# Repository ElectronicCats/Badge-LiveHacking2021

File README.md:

# Badge LiveHacking 2021

## Tecnologia

- Raspberry Pico
- LEDs
- Button
- USB

## Links

- [Raspberry Pico](https://www.raspberrypi.org/products/raspberry-pi-pico/)

## Agradecimientos
¿Quieres dar las gracias? Etiqueta a estas empresas en redes sociales y muestrales tu badge, gracias a ellos es posible

- [Mercado Libre](https://www.mercadolibre.com.mx/)
- [ElectronicCats](https://electroniccats.com/)

## License

Electronic Cats invests time and resources providing this open source design, please support Electronic Cats and open-source hardware by purchasing products from Electronic Cats!

Designed by Electronic Cats.

Hardware released under an CERN Open Hardware Licence v1.2. See the LICENSE_HARDWARE file for more information.

Electronic Cats is a registered trademark, please do not use if you sell these PCBs.

August 2021

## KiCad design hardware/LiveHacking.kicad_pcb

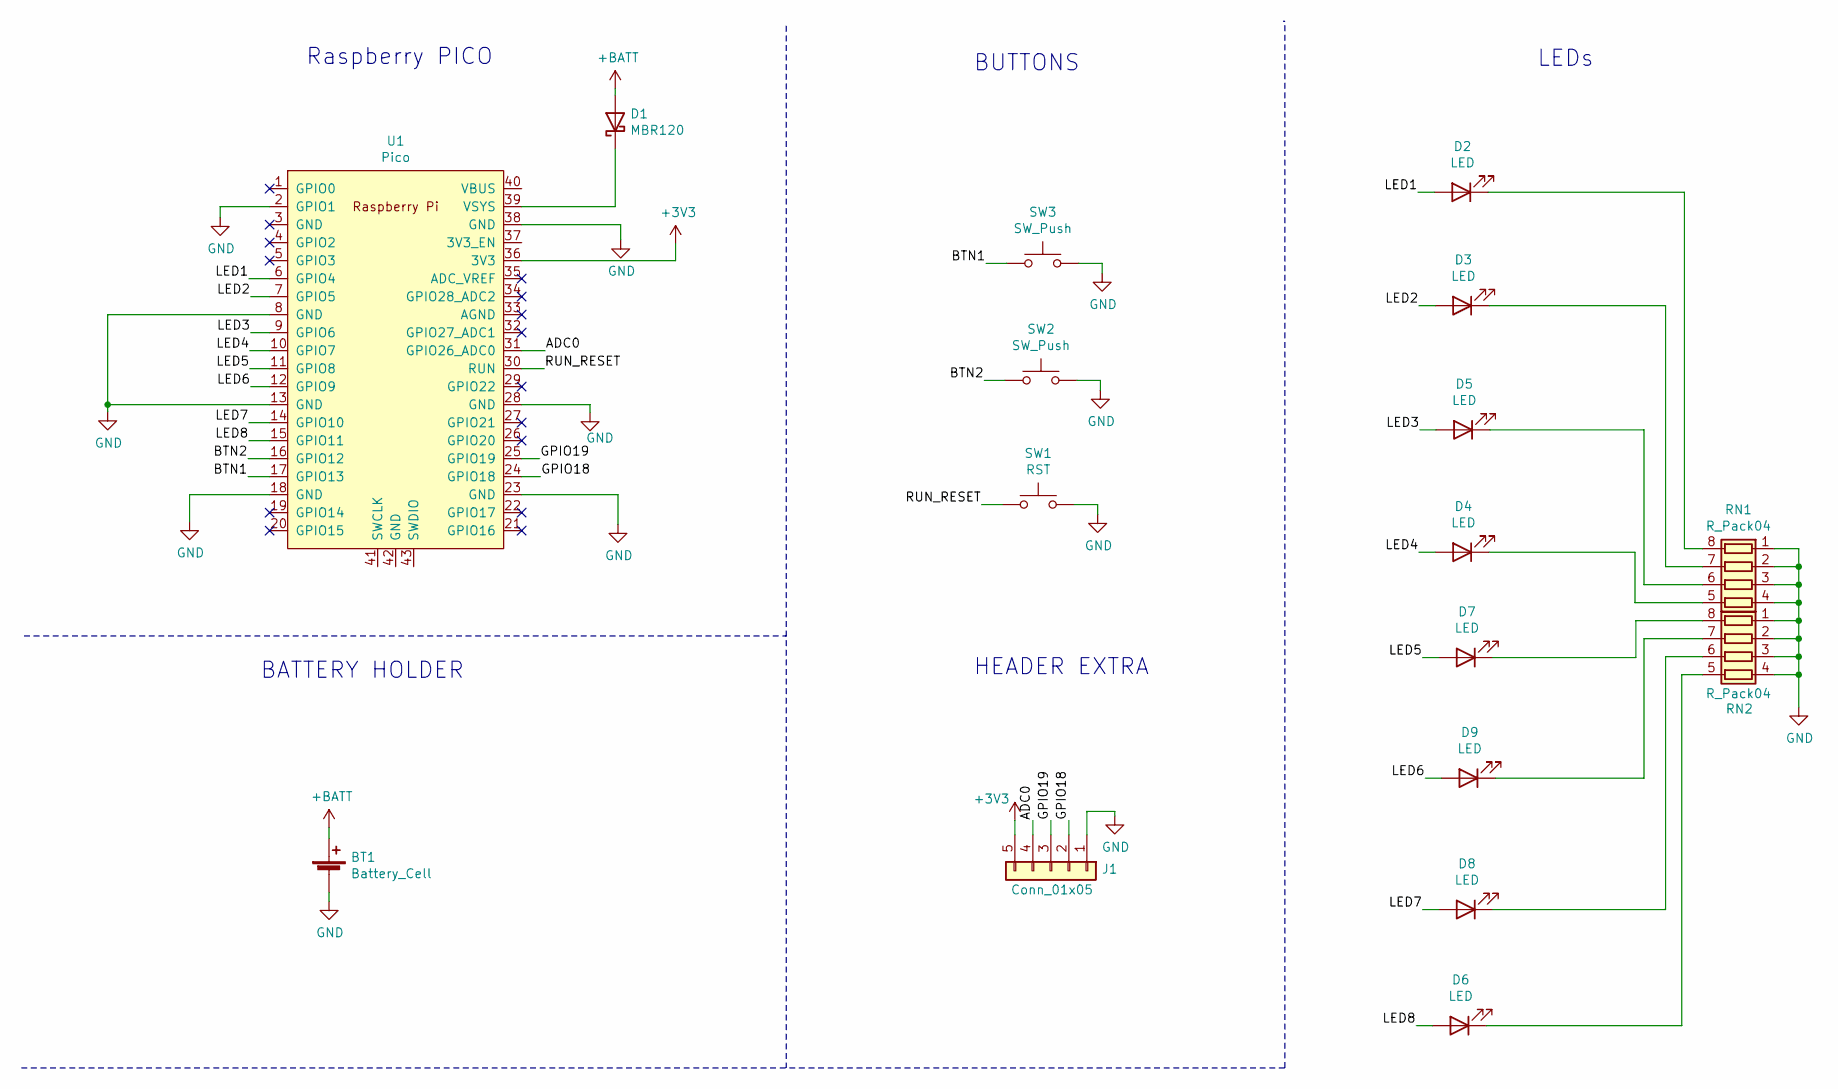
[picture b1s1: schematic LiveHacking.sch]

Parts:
BT1: Battery_Cell; 12BH423GR
D1: MBR120; D_SOD-123F
D2, D3, D4, D5, D6, D7, D8, D9: LED; LYT77K-K2M1-NoHole
J1: Conn_01x05; PinHeader_1x05_P2.54mm_Vertical
RN1, RN2: R_Pack04; R_Array_Convex_4x0603
SW1: RST; SW_SPST_TL3342
SW2, SW3: SW_Push; SW_SPST_TL3342
U1: Pico; RPi_Pico_SMD_TH

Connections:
+3V3: J1.5, U1.36 (3V3)
+BATT: BT1.1 (+), D1.2 (A)
/ADC0: J1.4, U1.31 (GPIO26_ADC0)
/BTN1: SW3.1, U1.17 (GPIO13)
/BTN2: SW2.1, U1.16 (GPIO12)
/GPIO18: J1.2, U1.24 (GPIO18)
/GPIO19: J1.3, U1.25 (GPIO19)
/LED1: D2.2 (A), U1.6 (GPIO4)
/LED2: D3.2 (A), U1.7 (GPIO5)
/LED3: D5.2 (A), U1.9 (GPIO6)
/LED4: D4.2 (A), U1.10 (GPIO7)
/LED5: D7.2 (A), U1.11 (GPIO8)
/LED6: D9.2 (A), U1.12 (GPIO9)
/LED7: D8.2 (A), U1.14 (GPIO10)
/LED8: D6.2 (A), U1.15 (GPIO11)
/RUN_RESET: SW1.1, U1.30 (RUN)
GND: BT1.2 (-), J1.1, RN1.1 (R1.1), RN1.2 (R2.1), RN1.3 (R3.1), RN1.4 (R4.1), RN2.1 (R1.1), RN2.2 (R2.1), RN2.3 (R3.1), RN2.4 (R4.1), SW1.2, SW2.2, SW3.2, U1.2 (GPIO1), U1.8 (GND), U1.13 (GND), U1.18 (GND), U1.23 (GND), U1.28 (GND), U1.38 (GND)
unnamed: D1.1 (K), U1.39 (VSYS)
unnamed: D2.1 (K), RN1.8 (R1.2)
unnamed: D3.1 (K), RN1.7 (R2.2)
unnamed: D4.1 (K), RN1.5 (R4.2)
unnamed: D5.1 (K), RN1.6 (R3.2)
unnamed: D6.1 (K), RN2.5 (R4.2)
unnamed: D7.1 (K), RN2.8 (R1.2)
unnamed: D8.1 (K), RN2.6 (R3.2)
unnamed: D9.1 (K), RN2.7 (R2.2)

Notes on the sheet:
Raspberry PICO
BUTTONS
LEDs
BATTERY HOLDER
HEADER EXTRA

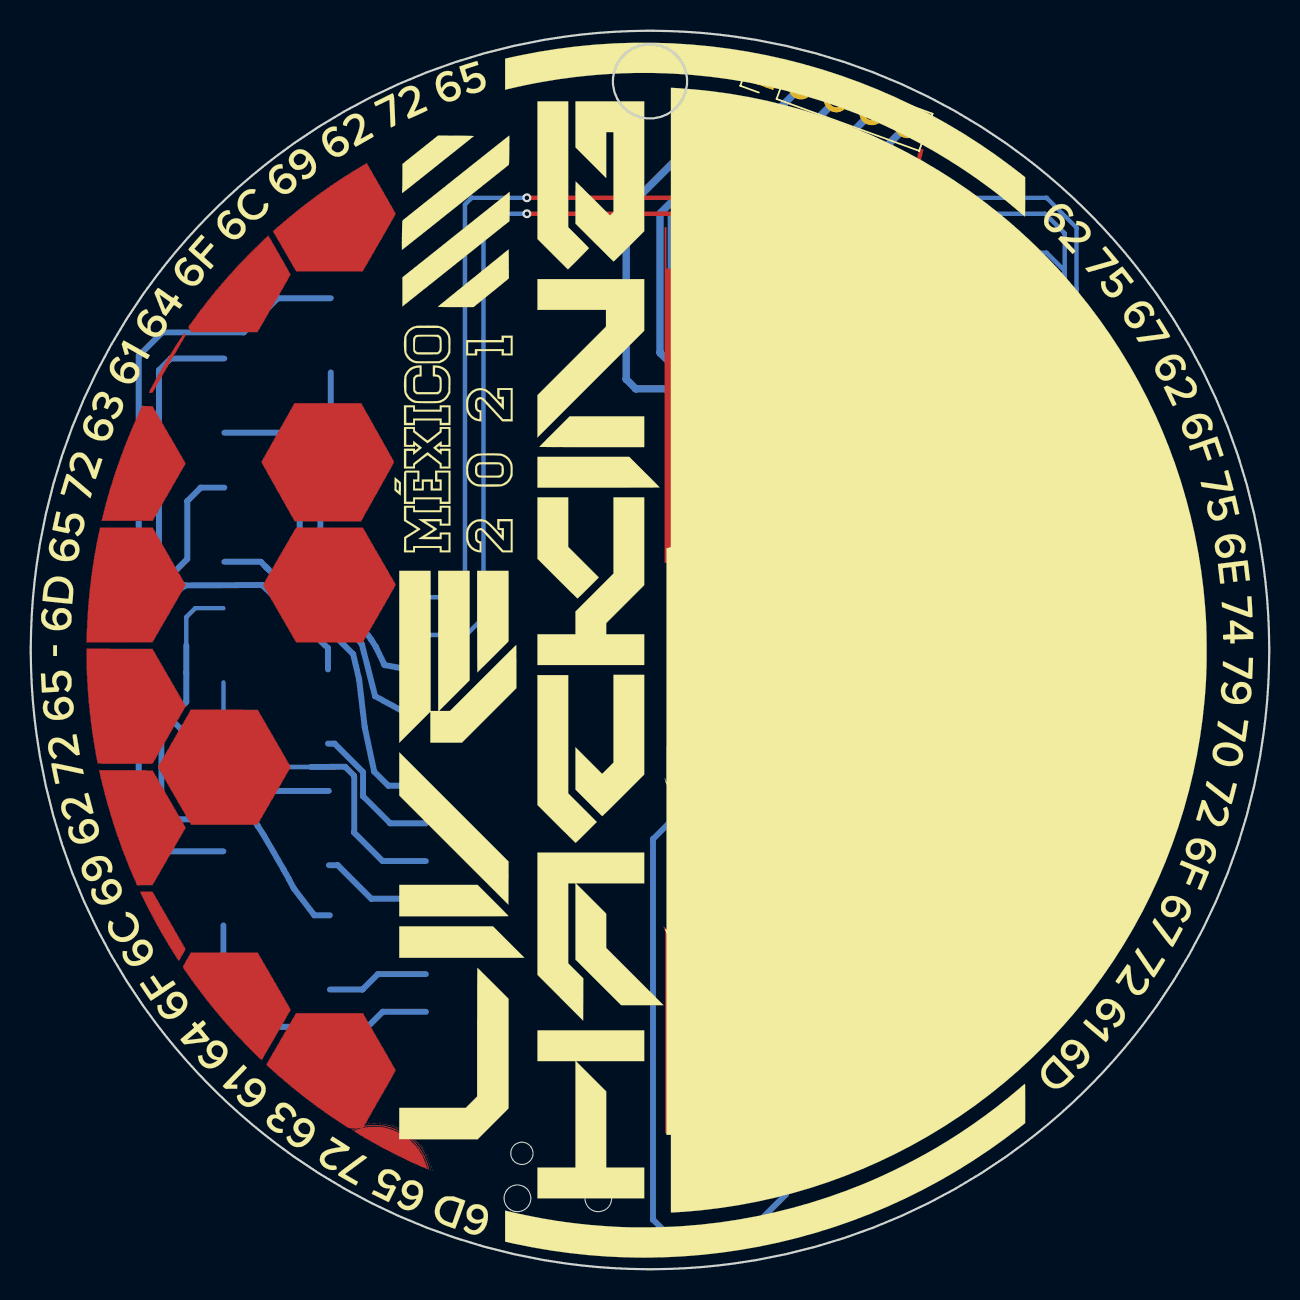
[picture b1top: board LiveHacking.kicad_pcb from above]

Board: 2 copper layers, 83.5 x 83.5 mm, 19 parts (0 on the bottom side), 26 nets.

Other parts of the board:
Ref**: Val**; logoMeli
Ref**#2: Val**; ML_LiveHacking_MLM

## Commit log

2021-08-14 init schematic
2021-08-15 add library
2021-08-15 add local libraries sch
2021-08-15 update project schmeatic start routing
2021-08-15 update holder
2021-08-15 add logo MercadoLibre and other labels
2021-08-15 add previews
2021-08-15 pre-release
2021-08-15 fix pads leds F.Bottom
2021-08-16 update ground plane
